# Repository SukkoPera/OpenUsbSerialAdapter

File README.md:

# OpenUsbSerialAdapter
OpenUsbSerialAdapter is an Open Hardware USB to TTL-level Serial converter.

### Summary
An infinite number of different models of USB to TTL-level serial converters can be found on every online shop, many of which even cost less than 1€ shipped from China, so why make one more? There are a few reasons:
- Many of them are missing the DTR and RTS signals (or at least do not break them out so that they can be used). At least one of these signals is necessary for programming Arduino boards through the serial port and, since this makes up for 90% of my use of USB to serial converters, I find this pretty annoying.
- Most of these cheap converters claim to be both 5V and 3.3V serial level compatible, but all most of them actually do is just use 3.3V signalling, which *usually* also works fine with boards that work at 5V, but still it is a bit of a hack.
- None of these converters has a decent 3.3V regulator onboard, usually being able to provide only a few tens of milliamperes on the 3.3V power pin (and not even all of them have one). This is too little for some uses, like powering an ESP8266 module for instance, and is the source of maaany of the problems users report with that chip.
- Finding Windows and OSX drivers for some of these modules is a nightmare.
- Not to mention the infamous FTDI-gate...

So, when I came across a USB to Serial chip ([Microchip MCP2200](http://ww1.microchip.com/downloads/en/DeviceDoc/200022228D.pdf)) that had RTS/CTS signals and claimed not to need any particular drivers, I decided to have a go at designing the one converter to rule them all. I tried to consider every possible feature during the design, but in any case I am releasing this as Open Hardware, so everybody can customize it so that it fully suits their needs.

### Features
- Real support for both 3.3V and 5V signalling and power output levels
- RX/TX leds
- Protection resistors for RX/TX inversion
- RX/TX pull-up resistors (optional)
- Can provide up to 1A current on the 3.3V power output pin (This will actually be less as it will be limited by USB)
- Hardware Flow Control pins (RTS/CTS, RTS can be used for the initial reset for Arduino programming)
- Speed up to 1000 kBaud/s
- Uses USB HID capabilities, which means it needs no drivers on Windows/OSX (This has to confirmed, as I only run Linux)
- Configurable product/manufacturer strings and PID/VID
- Ability to invert the polarity of the RX/TX signals
- Compact form factor (about the size of a standard thumb drive)
- Cheap (total BOM cost is less than 3€) and easy to DIY-build (about 20 common components, SMD soldering ability is required, but all components are 0805 or larger)

### Assembly and Configuration
Solder all components to the board in the order you prefer. You have some options:
- R3 and R4 are the RX/TX inversion protection resistors. I used 100 ohm for these, which works fine in my tests, but this value was improvised rather than calculated. You might want to increase them up to 1k for additional safety. In rare cases, you might want to replace them with 0 ohm/solder blobs, but this might be harmful for the main chip or for the device it is connected to. Do this at your risk.
- R5 and R6 are the RX/TX pull-up resistors. Usually these are not necessary, so you might want to skip them. Note that R7 is mandatory instead.

The adapter is somewhat configurable. On Windows you can use [the official Microchip Configuration Utility](http://ww1.microchip.com/downloads/en/DeviceDoc/MCP2200%20Configuration%20Utility%20v1.3.1.zip). On Linux (and OSX?) you can use [a quick replacement I put together](https://github.com/SukkoPera/OpenUsbSerialAdapter/tree/master/confutil), or [this other one](https://github.com/andrasbiro/mcp2200hid-linux). The latter is also capable of changing the USB product/manufacturer strings and PID/VID.

Note that the factory settings of the chip will NOT make the RX/TX leds blink on traffic, you will have to enable that through the configuration utility. Another apparent oddity is that you need to turn Hardware Flow Control OFF in order to use the adapter for Arduino programming.

Signal polarity inversion can also be enabled through the Configuration Utility.

### Usage
Just plug the converter into a free USB port of your computer. On Linux a /dev/ttyACMx device should pop up within seconds. On other Operating Systems... You are on your own :). In theory, it should not need any dedicated drivers, but I saw there are some [on the MCP2200 product page](https://www.microchip.com/wwwproducts/en/en546923), so you can get them from there, in case.

### Releases
If you want to get this board produced, you are recommended to get [the latest release](https://github.com/SukkoPera/OpenUsbSerialAdapter/releases) rather than the current git version, as the latter might be under development and is not guaranteed to be working.

Every release is accompanied by its Bill Of Materials (BOM) file and any relevant notes about it, which you are recommended to read carefully.

### License
The OpenUsbSerialAdapter documentation, including the design itself, is copyright &copy; SukkoPera 2020.

OpenUsbSerialAdapter is Open Hardware licensed under the [CERN OHL v. 1.2](http://ohwr.org/cernohl).

You may redistribute and modify this documentation under the terms of the CERN OHL v.1.2. This documentation is distributed *as is* and WITHOUT ANY EXPRESS OR IMPLIED WARRANTIES whatsoever with respect to its functionality, operability or use, including, without limitation, any implied warranties OF MERCHANTABILITY, SATISFACTORY QUALITY, FITNESS FOR A PARTICULAR PURPOSE or infringement. We expressly disclaim any liability whatsoever for any direct, indirect, consequential, incidental or special damages, including, without limitation, lost revenues, lost profits, losses resulting from business interruption or loss of data, regardless of the form of action or legal theory under which the liability may be asserted, even if advised of the possibility or likelihood of such damages.

A copy of the full license is included in file [LICENSE.pdf](LICENSE.pdf), please refer to it for applicable conditions. In order to properly deal with its terms, please see file [LICENSE_HOWTO.pdf](LICENSE_HOWTO.pdf).

The contact points for information about manufactured Products (see section 4.2) are listed in file [PRODUCT.md](PRODUCT.md).

Any modifications made by Licensees (see section 3.4.b) shall be recorded in file [CHANGES.md](CHANGES.md).

The Documentation Location of the original project is https://github.com/SukkoPera/OpenUsbSerialAdapter/.

### Support the Project
If you want to support the project, you can order the boards from PCBWay through this link:

You get my gratitude and cheap, good quality PCBs, professionally-made. I get some credit that will help with this and [other projects](https://www.pcbway.com/project/member/shareproject/?bmbid=41100). You won't even have to worry about the various PCB options, it's all pre-configured for you!

If you still have to register to that site, [you can use this link](https://www.pcbway.com/setinvite.aspx?inviteid=41100) to get some bonus initial credit (and yield me some more).

You can also buy me a coffee if you want:

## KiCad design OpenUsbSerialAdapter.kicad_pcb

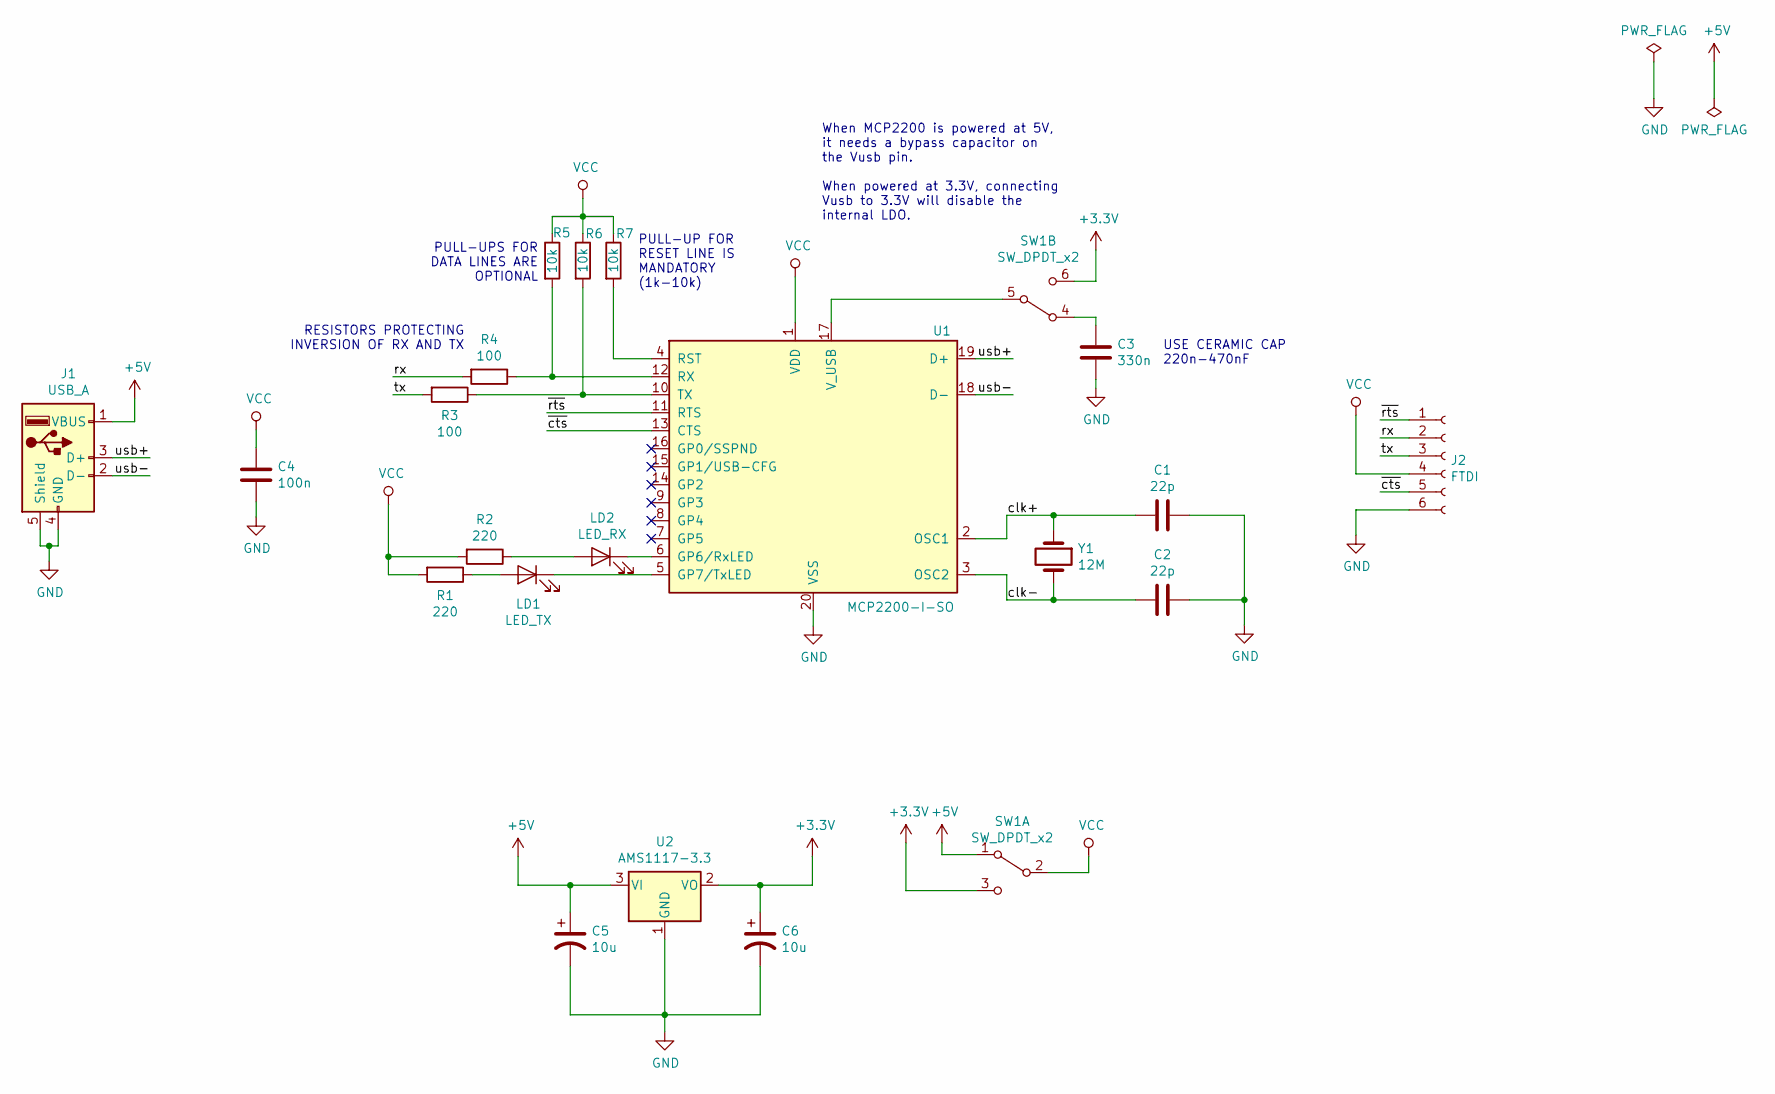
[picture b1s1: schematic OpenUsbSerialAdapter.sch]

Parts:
C1, C2: 22p; C_0805_2012Metric_Pad1.15x1.40mm_HandSolder
C3: 330n; C_1206_3216Metric_Pad1.42x1.75mm_HandSolder
C4: 100n; C_0805_2012Metric_Pad1.15x1.40mm_HandSolder
C5, C6: 10u; CP_EIA-3216-18_Kemet-A_Pad1.58x1.35mm_HandSolder
J1: USB_A; USB_A_Molex_48037
J2: FTDI; PinHeader_1x06_P2.54mm_Vertical
LD1: LED_TX; LED_0805_2012Metric_Pad1.15x1.40mm_HandSolder
LD2: LED_RX; LED_0805_2012Metric_Pad1.15x1.40mm_HandSolder
R1, R2: 220; R_0805_2012Metric_Pad1.15x1.40mm_HandSolder
R3, R4: 100; R_0805_2012Metric_Pad1.15x1.40mm_HandSolder
R5, R6, R7: 10k; R_0805_2012Metric_Pad1.15x1.40mm_HandSolder
SW1: SW_DPDT_x2; SW_DPDT
U1: MCP2200-I-SO; SOIC-20W_7.5x12.8mm_P1.27mm
U2: AMS1117-3.3; SOT-223-3_TabPin2
Y1: 12M; Crystal_HC49-U_Vertical

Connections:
+3V3: C6.1, SW1.3 (C), SW1.6 (C), U2.2 (VO)
+5V: C5.1, J1.1 (VBUS), SW1.1 (A), U2.3 (VI)
/clk+: C1.2, U1.2 (OSC1), Y1.1
/clk-: C2.2, U1.3 (OSC2), Y1.2
/rx: J2.2, R4.2
/tx: J2.3, R3.2
/usb+: J1.3 (D+), U1.19 (D+)
/usb-: J1.2 (D-), U1.18 (D-)
/~cts: J2.5, U1.13 (CTS)
/~rts: J2.1, U1.11 (RTS)
GND: C1.1, C2.1, C3.2, C4.2, C5.2, C6.2, J1.4 (GND), J1.5 (Shield), J2.6, U1.20 (VSS), U2.1 (GND)
unnamed: C3.1, SW1.4 (A)
unnamed: LD1.1 (K), U1.5 (GP7/TxLED)
unnamed: LD1.2 (A), R1.1
unnamed: LD2.1 (K), U1.6 (GP6/RxLED)
unnamed: LD2.2 (A), R2.1
unnamed: R3.1, R6.2, U1.10 (TX)
unnamed: R4.1, R5.2, U1.12 (RX)
unnamed: R7.2, U1.4 (RST)
unnamed: SW1.5 (B), U1.17 (V_USB)
VCC: C4.1, J2.4, R1.2, R2.2, R5.1, R6.1, R7.1, SW1.2 (B), U1.1 (VDD)

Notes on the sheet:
PULL-UPS FOR DATA LINES ARE OPTIONAL
RESISTORS PROTECTING INVERSION OF RX AND TX
PULL-UP FOR RESET LINE IS MANDATORY (1k-10k)
USE CERAMIC CAP 220n-470nF
When MCP2200 is powered at 5V, it needs a bypass capacitor on the Vusb pin. When powered at 3.3V, connecting Vusb to 3.3V will disable the internal LDO.

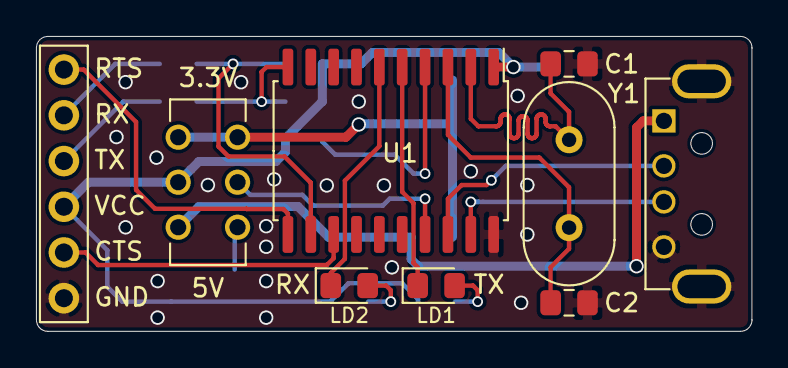
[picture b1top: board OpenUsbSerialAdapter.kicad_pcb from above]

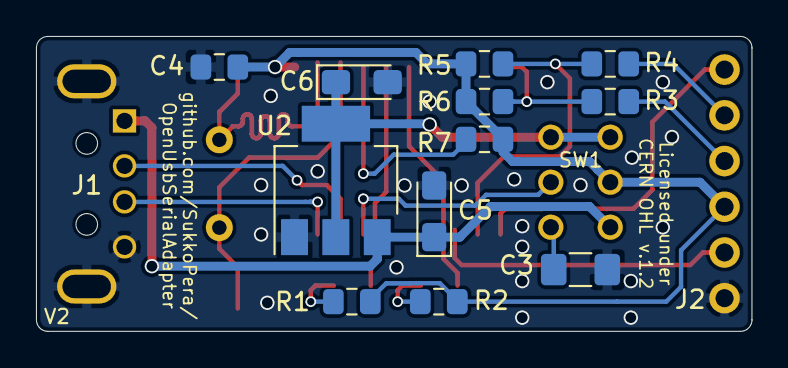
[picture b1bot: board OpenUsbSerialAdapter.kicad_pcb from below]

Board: 2 copper layers, 39.8 x 16.4 mm, 21 parts (12 on the bottom side), 21 nets.

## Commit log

2020-03-22 PCB is routed
2020-03-23 Remove fp-info-cache
2020-03-23 Done!
2020-03-23 Add docs
2020-03-23 Add renders
2020-03-23 Done! (Again...)
2020-03-23 Some refinements
2020-03-23 Final touches
2020-03-23 Add license
2020-03-24 Move track so that it looks better
2020-04-02 Add schematics PDF
2020-04-03 Tune quartz tracks length
2020-04-03 Final polishing
2020-04-04 Update version numbers
2020-05-01 Fix pin order of USB connector, sigh...
2020-05-04 Fix led labels, grrrrr!
2020-05-04 Add initial version of configuration utility
2021-01-15 Add doc

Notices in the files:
OpenUsbSerialAdapter.kicad_pcb:
Licensed under CERN OHL v.1.2
